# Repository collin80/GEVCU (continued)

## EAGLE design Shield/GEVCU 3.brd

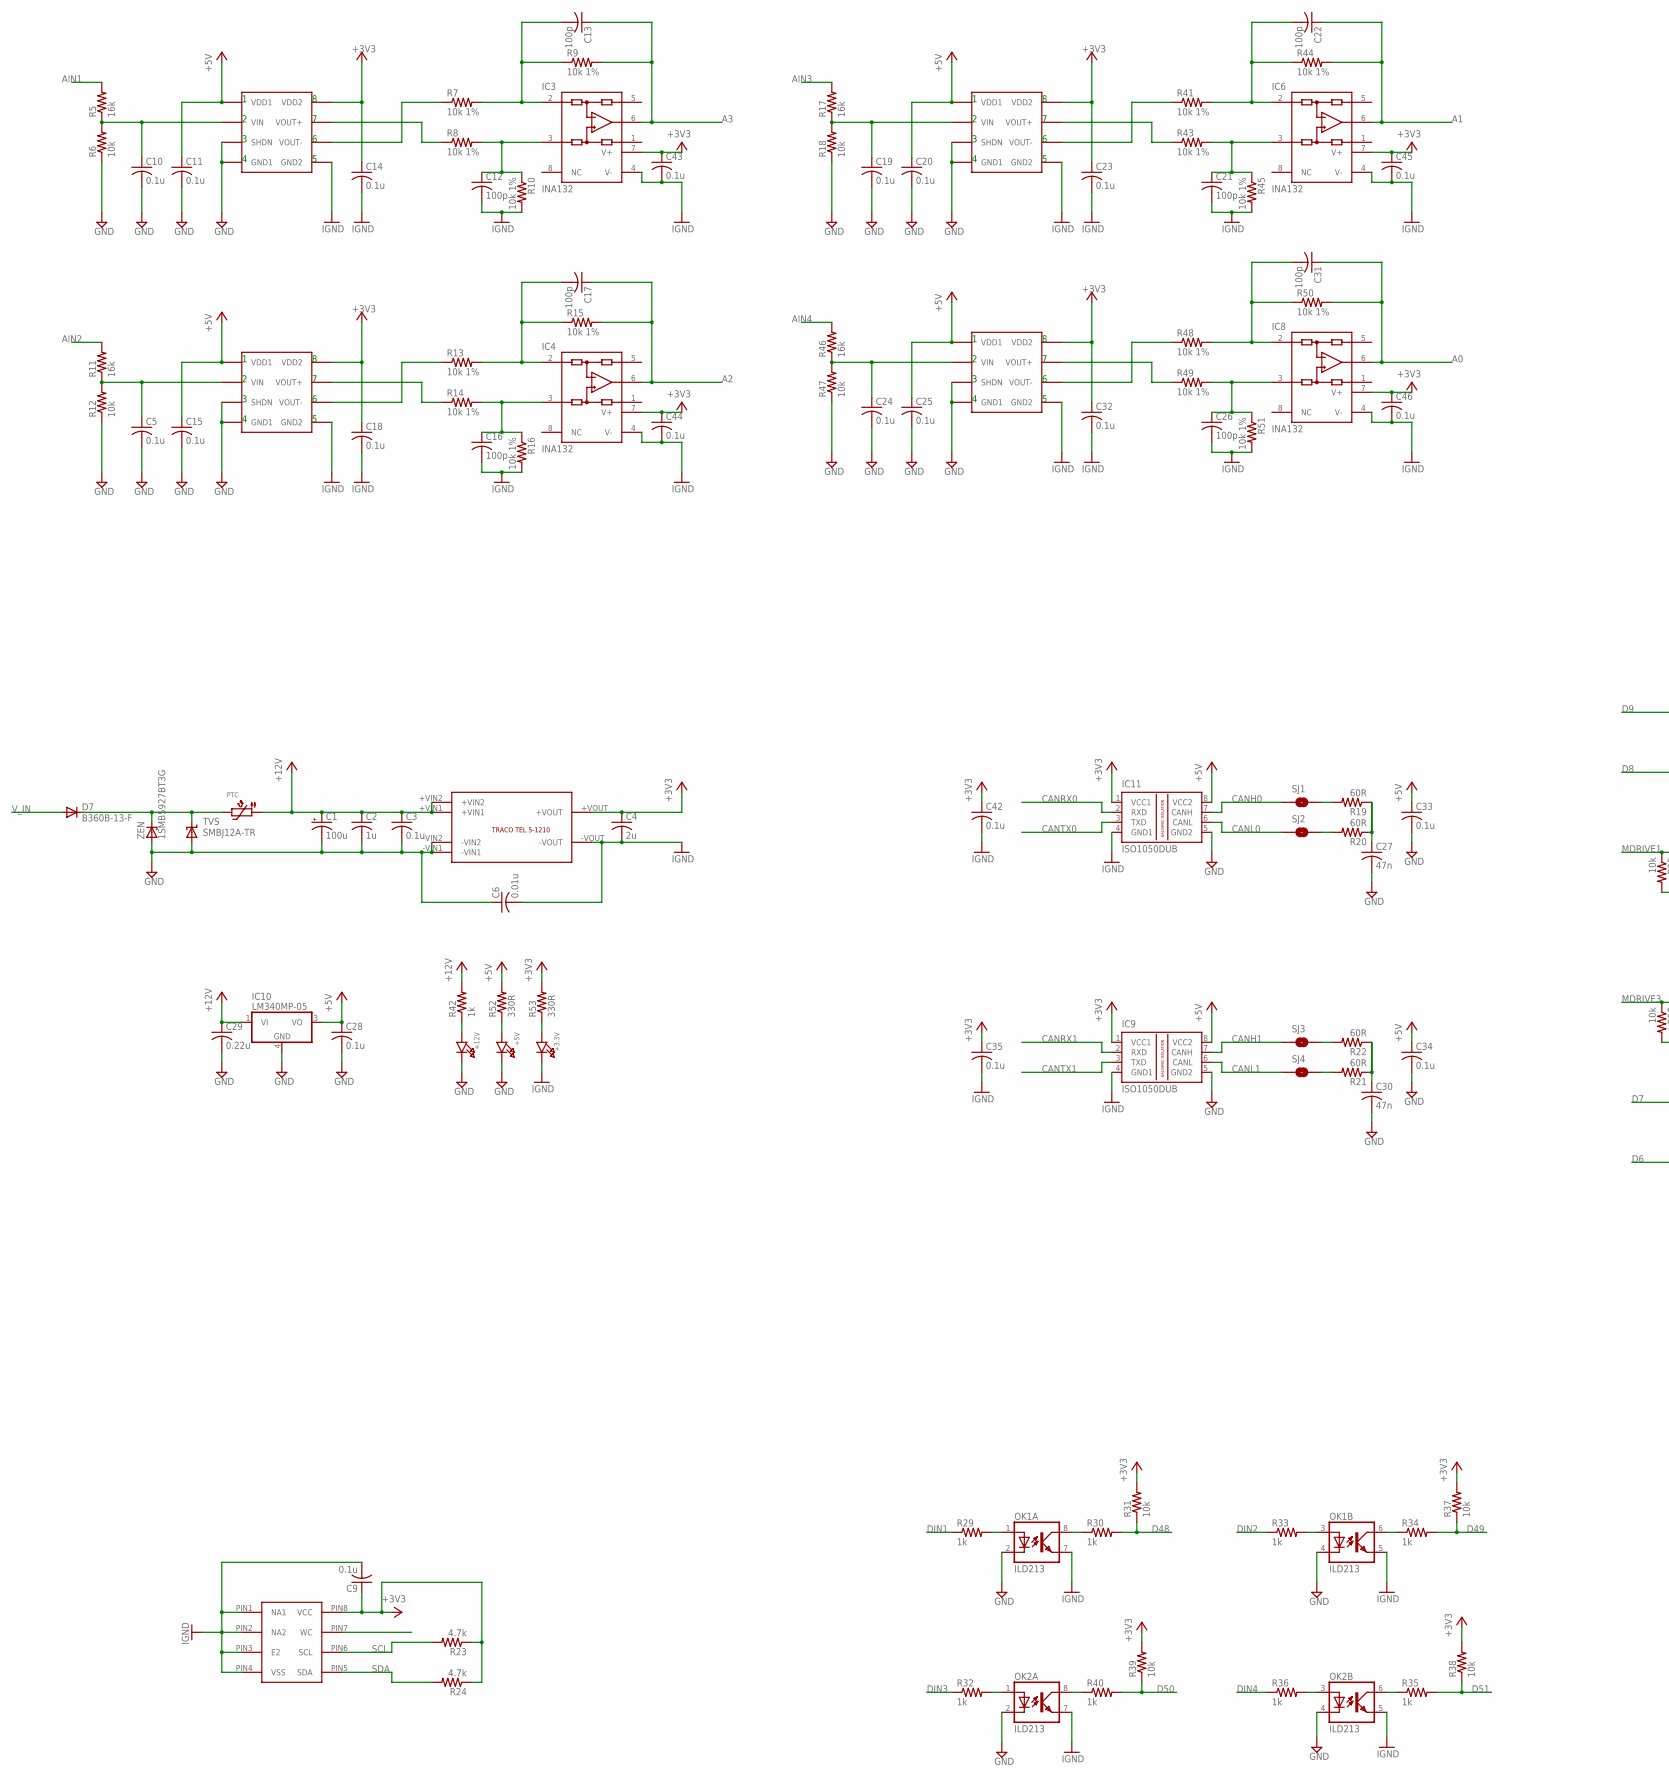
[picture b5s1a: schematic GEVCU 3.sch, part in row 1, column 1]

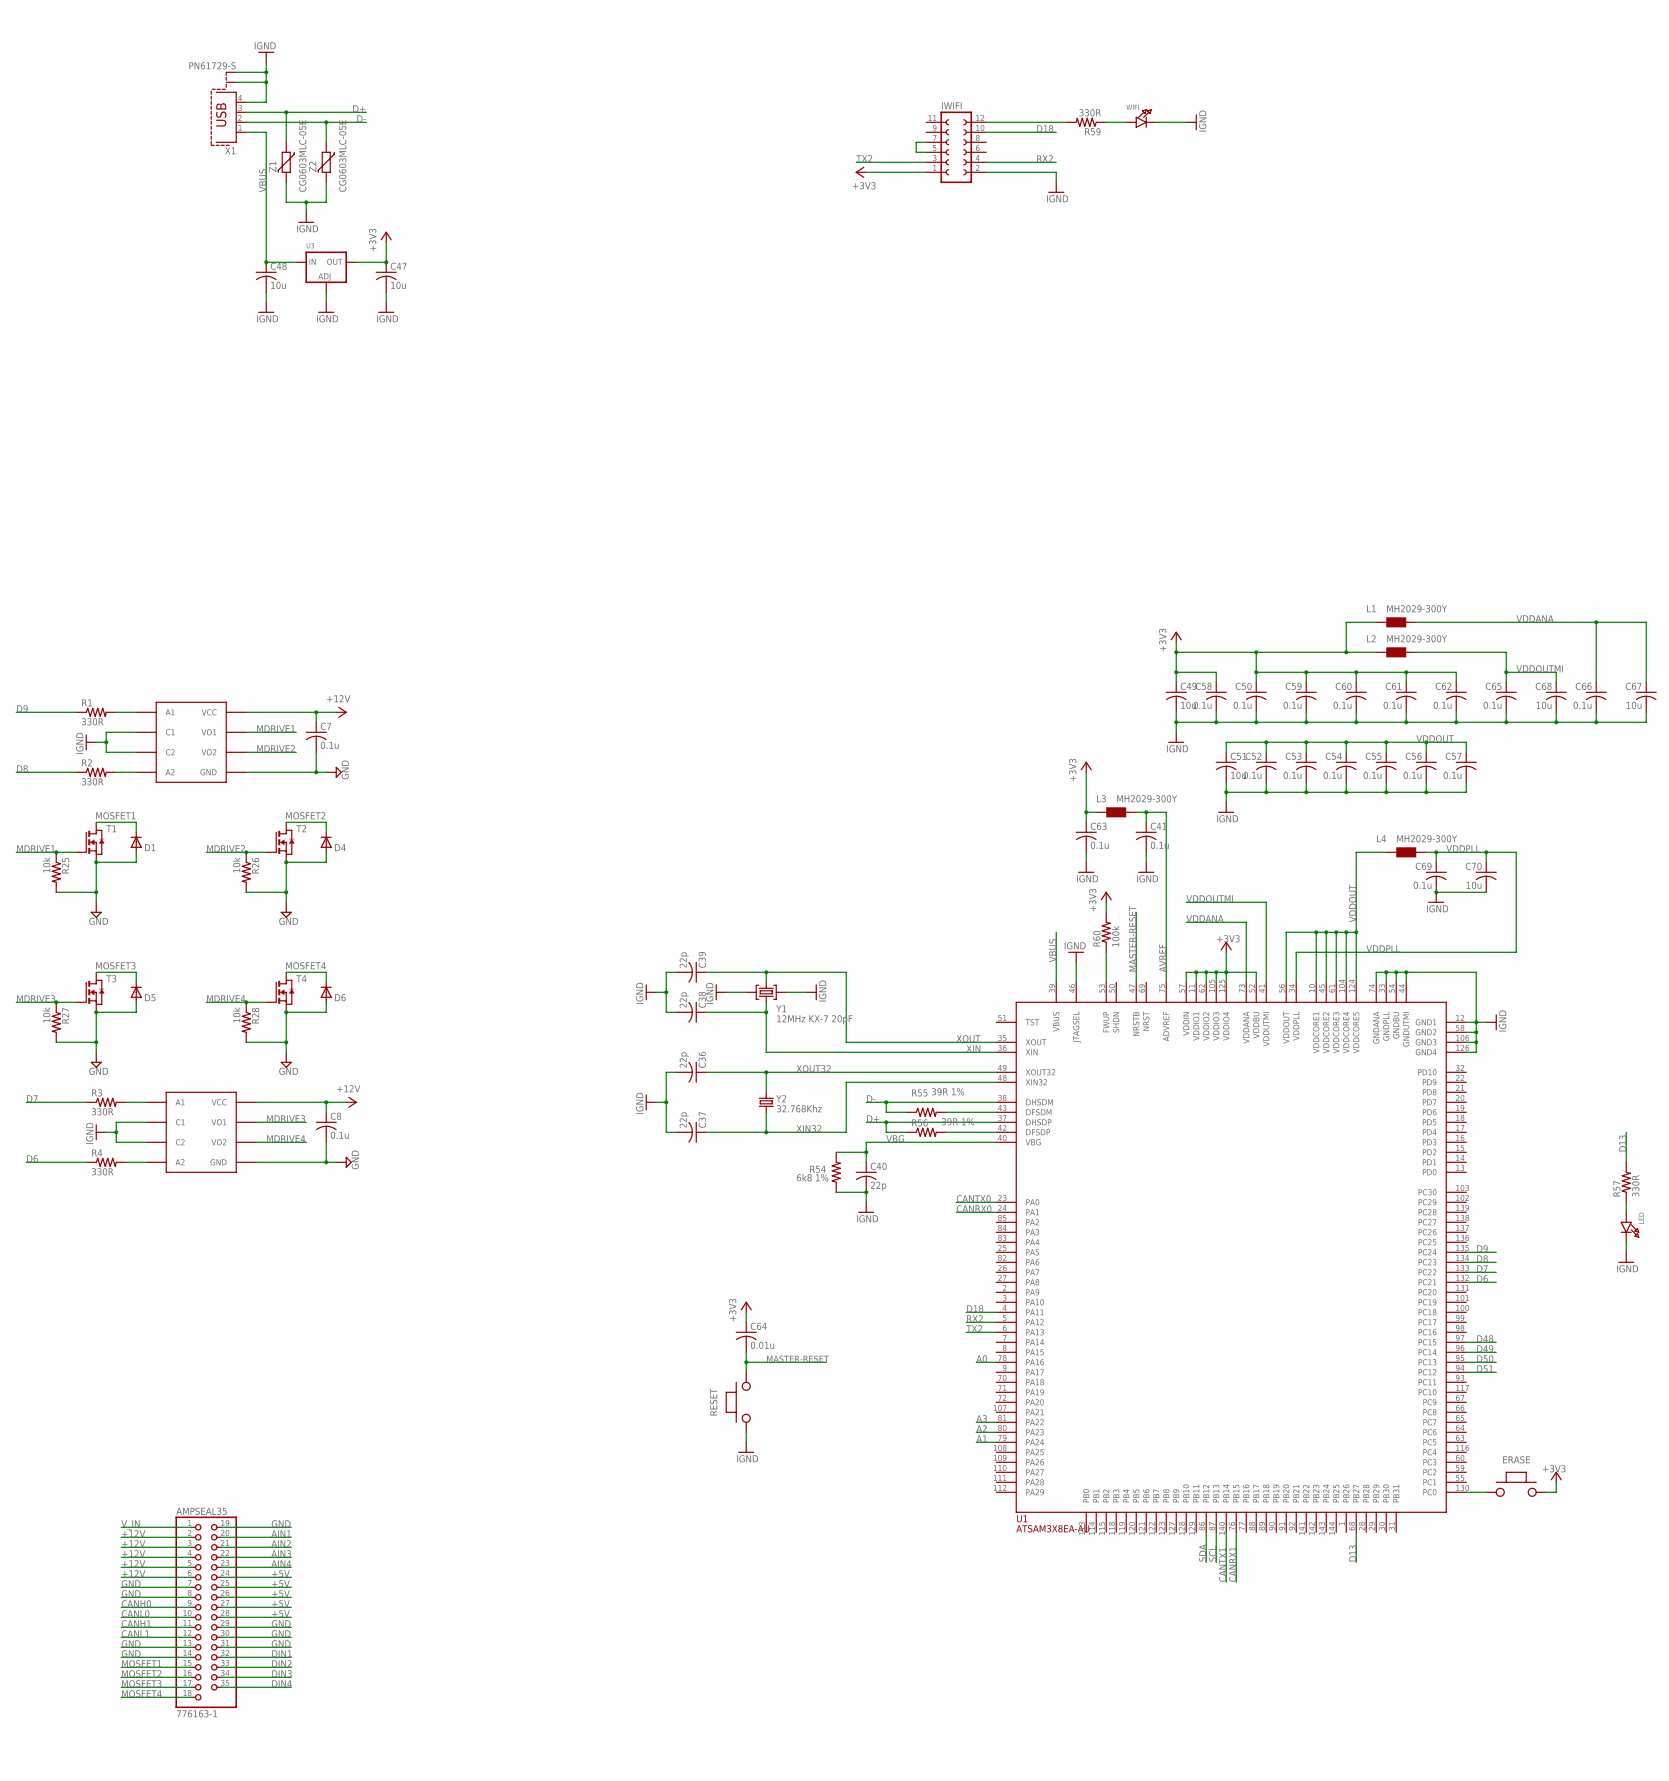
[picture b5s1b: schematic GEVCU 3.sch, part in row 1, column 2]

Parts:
+3.3V, +5V, +12V: LED0805; CHIPLED_0805
AMPSEAL35: 776163-1; AMPSEAL35
C1: 100u; E2,5-6
C2: 1u; C0805
C3, C5, C7, C8, C9, C10, C14, C18, C19, C23, C24, C28, C32, C33, C34, C35, C41, C42, C43, C44, C45, C46, C50, C52, C53, C54, C55, C56, C57, C58, C59, C60, C61, C62, C63, C65, C66, C69: 0.1u; C0805
C4: 2u; C0805
C6: 0.01u; C1812
C11, C15, C20, C25: 0.1u; C1206
C12, C13, C16, C17, C21, C22, C26, C31: 100p; C0805
C27, C30: 47n; C0805
C29: 0.22u; C0805
C36, C37, C40: 22p; C0805
C38, C39: 22p; C1206
C47, C48, C49, C51, C67, C68, C70: 10u; C0805
C64: 0.01u; C0805
D1, D4, D5, D6: MBR0520LT; SOD123
D7: B360B-13-F; SMB
ERASE: PUCHBUTTON
IC1, IC2, IC5, IC7: ACPL-C87A-000E; SO8-WIDE
IC3, IC4, IC6, IC8: INA132; SO08
IC9, IC11: ISO1050DUB; DUB-R-PDSO-G8
IC10: LM340MP-05; SOT223
IWIFI: FE06-2
L1, L2, L3, L4: MH2029-300Y; 0805
LED: LED0805; CHIPLED_0805
OK1, OK2: ILD213; SOIC08
PTC: PTC1812
R1, R2, R3, R4, R52, R53, R57, R59: 330R; R0805
R5, R11, R17, R46: 16k; R0805
R6, R12, R18, R25, R26, R27, R28, R31, R37, R38, R39, R47: 10k; R0805
R7, R8, R9, R10, R13, R14, R15, R16, R41, R43, R44, R45, R48, R49, R50, R51: 10k 1%; R0805
R19, R20, R21, R22: 60R; R0805
R23, R24: 4.7k; R0805
R29, R30, R32, R33, R34, R35, R36, R40, R42: 1k; R0805
R54: 6k8 1%; R0805
R55, R56: 39R 1%; R0805
R60: 100k; R0805
RESET: PUCHBUTTON
SJ1, SJ2, SJ3, SJ4: SOLDERJUMPERNO; SJ_2S-NO
T1, T2, T3, T4: NMOSSOT223; SOT223
TVS: SMBJ12A-TR; SMBJ
U1: ATSAM3X8EA-AU; LQFP144
U3: LM1117SOT223-WAVE; SOT223-W
U4, U5: SFH6731; DIP8
U6: M24M02-DRMN6TP; SOIC8
U$2: TRACO
WIFI: LED0805; CHIPLED_0805
X1: PN61729-S
Y1: 12MHz KX-7 20pF; CRYSTAL-3.2-2.5
Y2: 32.768Khz; RESONATOR_EPSON_FC_145
Z1, Z2: CG0603MLC-05E; CT/CN0603
ZEN: 1SMB5927BT3G; SMB

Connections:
+3V3: C4.1, C9.1, C14.1, C18.1, C23.1, C32.1, C35.1, C42.1, C43.1, C44.1, C45.1, C46.1, C47.1, C49.1, C50.1, C58.1, C59.1, C60.1, C61.1, C62.1, C63.1, C64.1, ERASE.P$2, IC1.8 (VDD2), IC2.8 (VDD2), IC3.7 (V+), IC4.7 (V+), IC5.8 (VDD2), IC6.7 (V+), IC7.8 (VDD2), IC8.7 (V+), IC9.1 (VCC1), IC11.1 (VCC1), IWIFI.1, L1.1, L2.1, L3.1, R23.1, R24.1, R31.2, R37.2, R38.2, R39.2, R53.2, R60.2, U1.11 (VDDIO1), U1.52 (VDDBU), U1.57 (VDDIN), U1.62 (VDDIO2), U1.105 (VDDIO3), U1.125 (VDDIO4), U3.2 (OUT), U6.PIN8 (VCC), U$2.+VOUT
+5V: AMPSEAL35.24, AMPSEAL35.25, AMPSEAL35.26, AMPSEAL35.27, AMPSEAL35.28, C11.1, C15.1, C20.1, C25.1, C28.1, C33.1, C34.1, IC1.1 (VDD1), IC2.1 (VDD1), IC5.1 (VDD1), IC7.1 (VDD1), IC9.8 (VCC2), IC10.3 (VO), IC11.8 (VCC2), R52.2
+12V: AMPSEAL35.2, AMPSEAL35.3, AMPSEAL35.4, AMPSEAL35.5, AMPSEAL35.6, C1.+, C2.1, C3.1, C7.1, C8.1, C29.1, IC10.1 (VI), PTC.P$1 (1), R42.2, U4.8 (VCC), U5.8 (VCC), U$2.+VIN1, U$2.+VIN2
A0: C31.1, IC8.6 (OUT), R50.2, U1.78 (PA16)
A1: C22.1, IC6.6 (OUT), R44.2, U1.79 (PA24)
A2: C17.1, IC4.6 (OUT), R15.2, U1.80 (PA23)
A3: C13.1, IC3.6 (OUT), R9.2, U1.81 (PA22)
AIN1: AMPSEAL35.20, R5.2
AIN2: AMPSEAL35.21, R11.2
AIN3: AMPSEAL35.22, R17.2
AIN4: AMPSEAL35.23, R46.2
AVREF: C41.1, L3.2, U1.75 (ADVREF)
CANH0: AMPSEAL35.9, IC11.7 (CANH), SJ1.1
CANH1: AMPSEAL35.11, IC9.7 (CANH), SJ3.1
CANL0: AMPSEAL35.10, IC11.6 (CANL), SJ2.1
CANL1: AMPSEAL35.12, IC9.6 (CANL), SJ4.1
CANRX0: IC11.2 (RXD), U1.24 (PA1)
CANRX1: IC9.2 (RXD), U1.76 (PB15)
CANTX0: IC11.3 (TXD), U1.23 (PA0)
CANTX1: IC9.3 (TXD), U1.140 (PB14)
D6: R4.1, U1.132 (PC21)
D7: R3.1, U1.133 (PC22)
D8: R2.1, U1.134 (PC23)
D9: R1.1, U1.135 (PC24)
D13: R57.2, U1.68 (PB27)
D18: IWIFI.10, U1.4 (PA11)
D48: R30.2, R31.1, U1.97 (PC15)
D49: R34.2, R37.1, U1.96 (PC14)
D50: R39.1, R40.2, U1.95 (PC13)
D51: R35.2, R38.1, U1.94 (PC12)
D+: R56.1, U1.37 (DHSDP), X1.3, Z1.1
D-: R55.1, U1.38 (DHSDM), X1.2, Z2.1
DIN1: AMPSEAL35.32, R29.1
DIN2: AMPSEAL35.33, R33.1
DIN3: AMPSEAL35.34, R32.1
DIN4: AMPSEAL35.35, R36.1
ERASE_S: ERASE.P$1, U1.130 (PC0)
GND: +5V.C, +12V.C, AMPSEAL35.7, AMPSEAL35.8, AMPSEAL35.13, AMPSEAL35.14, AMPSEAL35.19, AMPSEAL35.29, AMPSEAL35.30, AMPSEAL35.31, C1.-, C2.2, C3.2, C5.2, C6.1, C7.2, C8.2, C10.2, C11.2, C15.2, C19.2, C20.2, C24.2, C25.2, C27.2, C28.2, C29.2, C30.2, C33.2, C34.2, D1.A, D4.A, D5.A, D6.A, IC1.3 (SHDN), IC1.4 (GND1), IC2.3 (SHDN), IC2.4 (GND1), IC5.3 (SHDN), IC5.4 (GND1), IC7.3 (SHDN), IC7.4 (GND1), IC9.5 (GND2), IC10.4 (GND), IC11.5 (GND2), OK1.2 (C), OK1.4 (C), OK2.2 (C), OK2.4 (C), R6.1, R12.1, R18.1, R25.2, R26.2, R27.2, R28.2, R47.1, T1.3 (S), T2.3 (S), T3.3 (S), T4.3 (S), TVS.A, U4.5 (GND), U5.5 (GND), U$2.-VIN1, U$2.-VIN2, ZEN.A
IGND: +3.3V.C, C4.2, C6.2, C9.2, C12.2, C14.2, C16.2, C18.2, C21.2, C23.2, C26.2, C32.2, C35.2, C36.2, C37.2, C38.2, C39.2, C40.2, C41.2, C42.2, C43.2, C44.2, C45.2, C46.2, C47.2, C48.2, C49.2, C50.2, C51.2, C52.2, C53.2, C54.2, C55.2, C56.2, C57.2, C58.2, C59.2, C60.2, C61.2, C62.2, C63.2, C65.2, C66.2, C67.2, C68.2, C69.2, C70.2, IC1.5 (GND2), IC2.5 (GND2), IC3.4 (V-), IC4.4 (V-), IC5.5 (GND2), IC6.4 (V-), IC7.5 (GND2), IC8.4 (V-), IC9.4 (GND1), IC11.4 (GND1), IWIFI.2, LED.C, OK1.5 (EMIT), OK1.7 (EMIT), OK2.5 (EMIT), OK2.7 (EMIT), R10.2, R16.2, R45.2, R51.2, R54.1, RESET.P$1, U1.12 (GND1), U1.33 (GNDPLL), U1.44 (GNDUTMI), U1.46 (JTAGSEL), U1.54 (GNDBU), U1.58 (GND2), U1.74 (GNDANA), U1.106 (GND3), U1.126 (GND4), U3.1 (ADJ), U4.2 (C1), U4.3 (C2), U5.2 (C1), U5.3 (C2), U6.PIN1 (NA1), U6.PIN2 (NA2), U6.PIN3 (E2), U6.PIN4 (VSS), U$2.-VOUT, WIFI.C, X1.4, X1.S1, X1.S2, Y1.2 (GND), Y1.4 (GND), Z1.2, Z2.2
MASTER-RESET: C64.2, RESET.P$2, U1.47 (NRSTB)
MDRIVE1: R25.1, T1.1 (G), U5.7 (VO1)
MDRIVE2: R26.1, T2.1 (G), U5.6 (VO2)
MDRIVE3: R27.1, T3.1 (G), U4.7 (VO1)
MDRIVE4: R28.1, T4.1 (G), U4.6 (VO2)
MOSFET1: AMPSEAL35.15, D1.C, T1.2 (D), T1.4 (D)
MOSFET2: AMPSEAL35.16, D4.C, T2.2 (D), T2.4 (D)
MOSFET3: AMPSEAL35.17, D5.C, T3.2 (D), T3.4 (D)
MOSFET4: AMPSEAL35.18, D6.C, T4.2 (D), T4.4 (D)
unnamed: C10.1, IC1.2 (VIN), R5.1, R6.2
unnamed: +3.3V.A, R53.1
unnamed: D7.C, PTC.P$2 (2), TVS.C, ZEN.C
unnamed: +5V.A, R52.1
unnamed: R3.2, U4.1 (A1)
unnamed: LED.A, R57.1
unnamed: R1.2, U5.1 (A1)
unnamed: IC2.7 (VOUT+), R14.1
unnamed: IC2.6 (VOUT-), R13.1
unnamed: R2.2, U5.4 (A2)
unnamed: R4.2, U4.4 (A2)
unnamed: C17.2, IC4.2 (-IN), R13.2, R15.1
unnamed: IC1.7 (VOUT+), R8.1
unnamed: IC1.6 (VOUT-), R7.1
unnamed: C13.2, IC3.2 (-IN), R7.2, R9.1
unnamed: C12.1, IC3.3 (+IN), R8.2, R10.1
unnamed: C16.1, IC4.3 (+IN), R14.2, R16.1
unnamed: C5.1, IC2.2 (VIN), R11.1, R12.2
unnamed: IC5.7 (VOUT+), R43.1
unnamed: IC5.6 (VOUT-), R41.1
unnamed: C22.2, IC6.2 (-IN), R41.2, R44.1
unnamed: C21.1, IC6.3 (+IN), R43.2, R45.1
unnamed: C19.1, IC5.2 (VIN), R17.1, R18.2
unnamed: C27.1, R19.1, R20.1
unnamed: IC7.7 (VOUT+), R49.1
unnamed: R19.2, SJ1.2
unnamed: R20.2, SJ2.2
unnamed: R21.2, SJ4.2
unnamed: C30.1, R21.1, R22.1
unnamed: R22.2, SJ3.2
unnamed: OK1.1 (A), R29.2
unnamed: OK1.3 (A), R33.2
unnamed: OK1.8 (COL), R30.1
unnamed: OK1.6 (COL), R34.1
unnamed: IC7.6 (VOUT-), R48.1
unnamed: OK2.6 (COL), R35.1
unnamed: C31.2, IC8.2 (-IN), R48.2, R50.1
unnamed: OK2.8 (COL), R40.1
unnamed: C26.1, IC8.3 (+IN), R49.2, R51.1
unnamed: OK2.1 (A), R32.2
unnamed: C24.1, IC7.2 (VIN), R46.1, R47.2
unnamed: OK2.3 (A), R36.2
unnamed: +12V.A, R42.1
unnamed: IWIFI.12, R59.2
unnamed: R59.1, WIFI.A
unnamed: IWIFI.5, IWIFI.7
unnamed: R55.2, U1.43 (DFSDM)
unnamed: R56.2, U1.42 (DFSDP)
unnamed: R60.1, U1.53 (FWUP)
RX2: IWIFI.4, U1.5 (PA12)
RXD1: U6.PIN7 (WC)
SCL: R23.2, U1.87 (PB13), U6.PIN6 (SCL)
SDA: R24.2, U1.86 (PB12), U6.PIN5 (SDA)
TX2: IWIFI.3, U1.6 (PA13)
VBG: C40.1, R54.2, U1.40 (VBG)
VBUS: C48.1, U1.39 (VBUS), U3.3 (IN), X1.1
VDDANA: C66.1, C67.1, L1.2, U1.73 (VDDANA)
VDDOUT: C51.1, C52.1, C53.1, C54.1, C55.1, C56.1, C57.1, L4.1, U1.10 (VDDCORE1), U1.45 (VDDCORE2), U1.56 (VDDOUT), U1.61 (VDDCORE3), U1.104 (VDDCORE4), U1.124 (VDDCORE5)
VDDOUTMI: C65.1, C68.1, L2.2, U1.41 (VDDUTMI)
VDDPLL: C69.1, C70.1, L4.2, U1.34 (VDDPLL)
V_IN: AMPSEAL35.1, D7.A
XIN: C38.1, U1.36 (XIN), Y1.1 (C1)
XIN32: C37.1, U1.48 (XIN32), Y2.P$2 (2)
XOUT: C39.1, U1.35 (XOUT), Y1.3 (C2)
XOUT32: C36.1, U1.49 (XOUT32), Y2.P$1 (1)

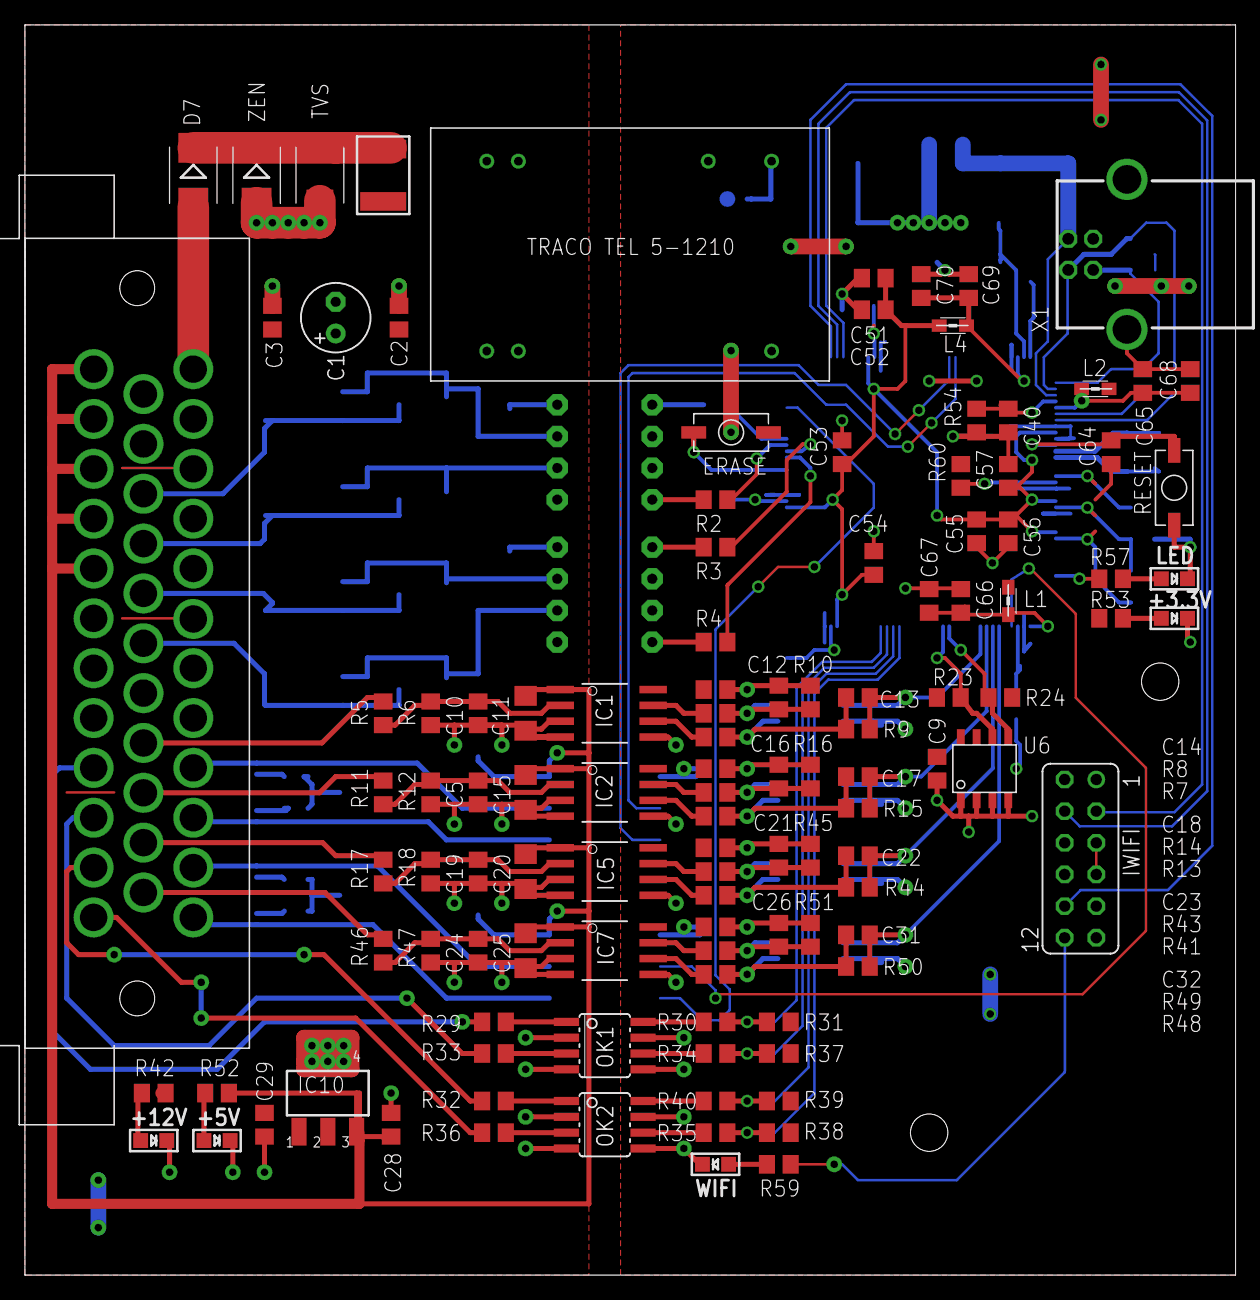
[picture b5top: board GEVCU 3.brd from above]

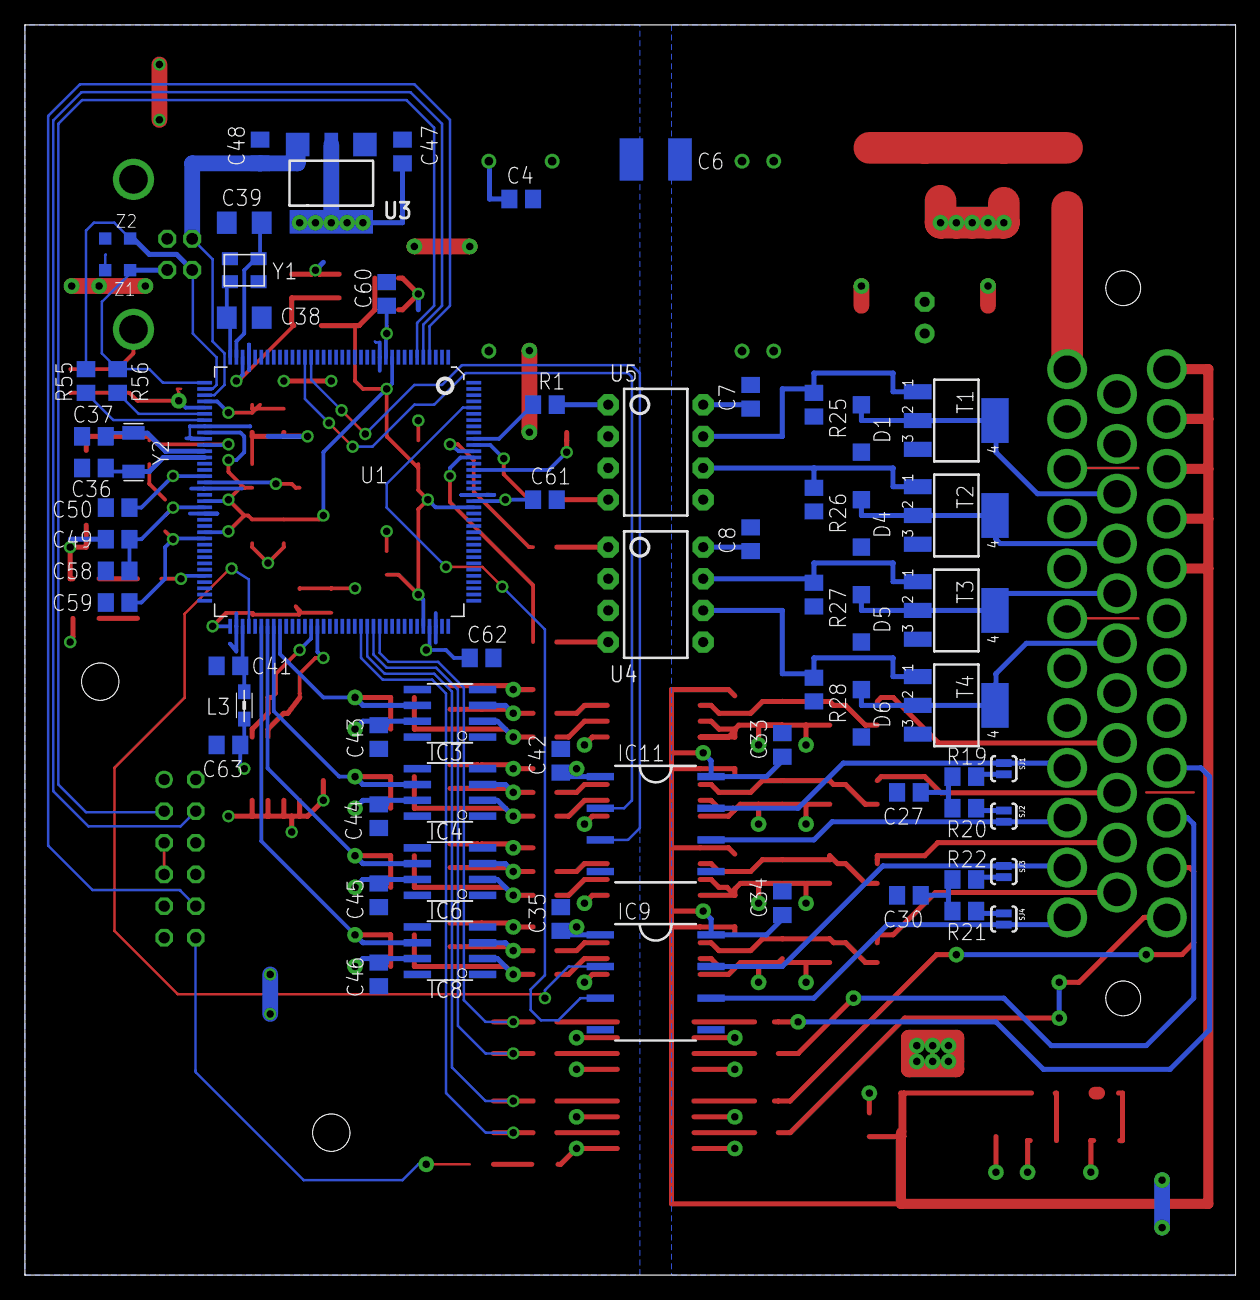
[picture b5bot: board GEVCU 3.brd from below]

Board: 2 copper layers, 97.2 x 100.3 mm, 182 parts (67 on the bottom side), 112 nets.

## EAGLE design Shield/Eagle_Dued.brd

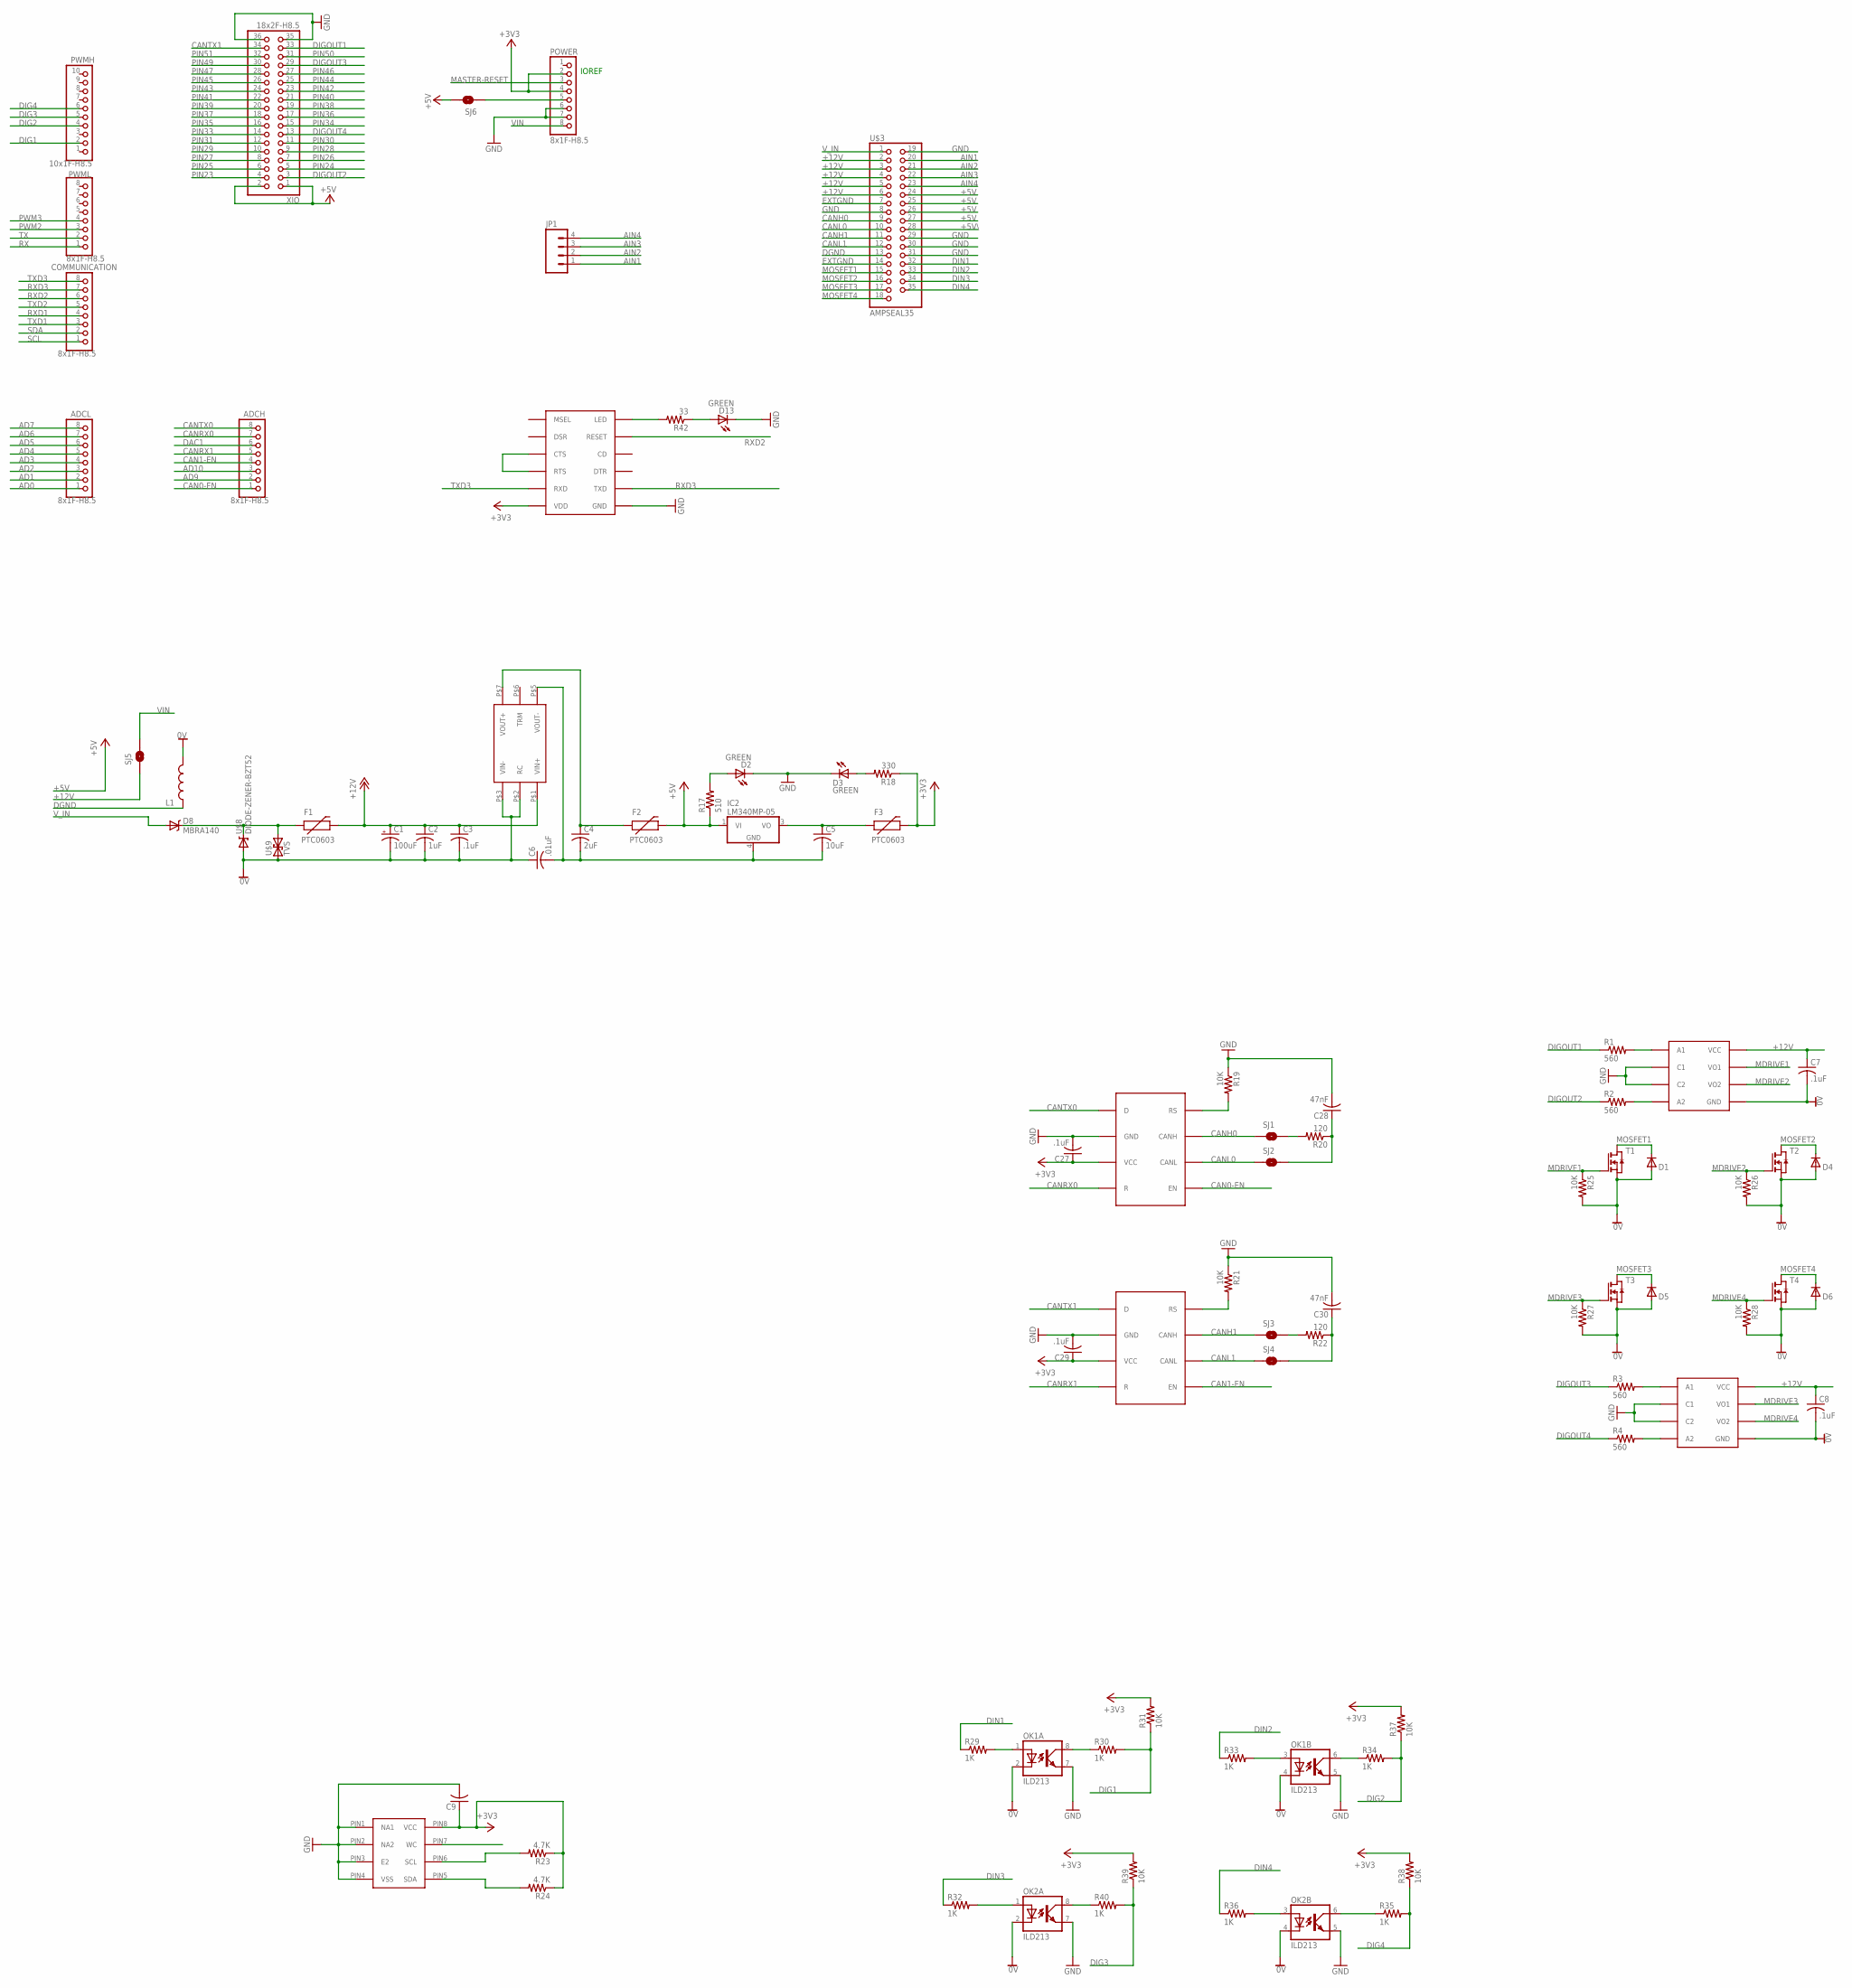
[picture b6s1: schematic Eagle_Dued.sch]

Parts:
ADCH: 8x1F-H8.5; 1X08
ADCL: 8x1F-H8.5; 1X08
C1: 100uF; E2,5-6
C2: 1uF; C1206
C3, C7, C8: .1uF; C1206
C4: 2uF; C0805
C5: 10uF; C1206
C6: .01uF; C1206
C9: C-USC0603; C0603
C27, C29: .1uF; C0603
C28, C30: 47nF; C0603
COMMUNICATION: 8x1F-H8.5; 1X08
D1, D4, D5, D6: MBR0520LT; SOD123
D2, D3, D13: GREEN; LED-0603
D8: MBRA140; SMA-DIODE
F1, F2, F3: PTC0603; 0603
IC2: LM340MP-05; SOT223
JP1: M04POLAR; MOLEX-1X4
L1: INDUCTOR1206H*; INDUCTOR-1206
OK1, OK2: ILD213; SOIC08
POWER: 8x1F-H8.5; 1X08
PWMH: 10x1F-H8.5; 1X10
PWML: 8x1F-H8.5; 1X08
R1, R2, R3, R4: 560; R0603
R17: 510; R0603
R18: 330; R0603
R19, R21, R25, R26, R27, R28, R31, R37, R38, R39: 10K; R0603
R20, R22: 120; R0603
R23, R24: 4.7K; R0603
R29, R30, R32, R33, R34, R35, R36, R40: 1K; R0603
R42: 33; R0603
SJ1, SJ2, SJ3, SJ4, SJ5, SJ6: SOLDERJUMPERNO; SJ_2S-NO
T1, T2, T3, T4: NMOSSOT223; SOT223
U$1: CC3-E
U$2, U$6: SN65HVD234; SOIC8
U$3: AMPSEAL35
U$4: MINIWIFI
U$5: M24M02-DRMN6TP; SOIC8
U$7, U$10: SFH6731; DIP8
U$8: DIODE-ZENER-BZT52; SOD-323
U$9: TVS; SMA-DIODE
XIO: 18x2F-H8.5; 2X18

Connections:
0V: C7.2, C8.2, OK1.2 (C), OK1.4 (C), OK2.2 (C), OK2.4 (C), U$7.5 (GND), U$10.5 (GND)
+3V3: C9.1, C27.1, C29.1, F3.2, POWER.2, POWER.4, R18.1, R23.1, R24.1, R31.2, R37.2, R38.2, R39.2, U$2.PIN3 (VCC), U$4.P$1 (VDD), U$5.PIN8 (VCC), U$6.PIN3 (VCC)
+5V: F2.2, IC2.1 (VI), R17.1, SJ6.2, U$3.24, U$3.25, U$3.26, U$3.27, XIO.1, XIO.2
+5V\: U$3.28
+12V: C1.+, C2.1, C3.1, C7.1, C8.1, F1.2, SJ5.1, U$1.P$1 (VIN+), U$3.2, U$3.3, U$3.4, U$3.5, U$3.6, U$7.8 (VCC), U$10.8 (VCC)
AD0: ADCL.1
AD1: ADCL.2
AD2: ADCL.3
AD3: ADCL.4
AD4: ADCL.5
AD5: ADCL.6
AD6: ADCL.7
AD7: ADCL.8
AD9: ADCH.2
AD10: ADCH.3
AIN1: JP1.1, U$3.20
AIN2: JP1.2, U$3.21
AIN3: JP1.3, U$3.22
AIN4: JP1.4, U$3.23
CAN0-EN: ADCH.1, U$6.PIN5 (EN)
CAN1-EN: ADCH.4, U$2.PIN5 (EN)
CANH0: SJ1.1, U$3.9, U$6.PIN7 (CANH)
CANH1: SJ3.1, U$2.PIN7 (CANH), U$3.11
CANL0: SJ2.1, U$3.10, U$6.PIN6 (CANL)
CANL1: SJ4.1, U$2.PIN6 (CANL), U$3.12
CANRX0: ADCH.7, U$6.PIN4 (R)
CANRX1: ADCH.5, U$2.PIN4 (R)
CANTX0: ADCH.8, U$6.PIN1 (D)
CANTX1: U$2.PIN1 (D), XIO.34
DAC1: ADCH.6
DGND: L1.P$1 (1), U$3.13
DIG1: PWMH.2, R30.2, R31.1
DIG2: PWMH.4, R34.2, R37.1
DIG3: PWMH.5, R39.1, R40.2
DIG4: PWMH.6, R35.2, R38.1
DIGOUT1: R1.1, XIO.33
DIGOUT2: R2.1, XIO.3
DIGOUT3: R3.1, XIO.29
DIGOUT4: R4.1, XIO.13
DIN1: R29.1, U$3.32
DIN2: R33.1, U$3.33
DIN3: R32.1, U$3.34
DIN4: R36.1, U$3.35
EXTGND: C1.-, C2.2, C3.2, C6.1, D1.A, D4.A, D5.A, D6.A, L1.P$2 (2), R25.2, R26.2, R27.2, R28.2, T1.3 (S), T2.3 (S), T3.3 (S), T4.3 (S), U$1.P$2 (RC), U$1.P$3 (VIN-), U$3.7, U$3.14, U$8.2 (A), U$9.A (1)
GND: C4.2, C5.2, C6.2, C9.2, C27.2, C28.2, C29.2, C30.2, D2.C, D3.C, D13.C, IC2.4 (GND), OK1.5 (EMIT), OK1.7 (EMIT), OK2.5 (EMIT), OK2.7 (EMIT), POWER.6, POWER.7, R19.1, R21.1, U$1.P$5 (VOUT-), U$2.PIN2 (GND), U$3.8, U$3.19, U$3.29, U$3.30, U$3.31, U$4.P$2 (GND), U$5.PIN1 (NA1), U$5.PIN2 (NA2), U$5.PIN3 (E2), U$5.PIN4 (VSS), U$6.PIN2 (GND), U$7.2 (C1), U$7.3 (C2), U$10.2 (C1), U$10.3 (C2), XIO.35, XIO.36
MASTER-RESET: POWER.3
MDRIVE1: R25.1, T1.1 (G), U$10.7 (VO1)
MDRIVE2: R26.1, T2.1 (G), U$10.6 (VO2)
MDRIVE3: R27.1, T3.1 (G), U$7.7 (VO1)
MDRIVE4: R28.1, T4.1 (G), U$7.6 (VO2)
MOSFET1: D1.C, T1.2 (D), T1.4 (D), U$3.15
MOSFET2: D4.C, T2.2 (D), T2.4 (D), U$3.16
MOSFET3: D5.C, T3.2 (D), T3.4 (D), U$3.17
MOSFET4: D6.C, T4.2 (D), T4.4 (D), U$3.18
unnamed: POWER.5, SJ6.1
unnamed: U$4.P$5 (RTS), U$4.P$7 (CTS)
unnamed: D8.C, F1.1, U$8.1 (C), U$9.C (2)
unnamed: R42.2, U$4.P$12 (LED)
unnamed: R3.2, U$7.1 (A1)
unnamed: C4.1, F2.1, U$1.P$7 (VOUT+)
unnamed: R1.2, U$10.1 (A1)
unnamed: C5.1, F3.1, IC2.3 (VO)
unnamed: D13.A, R42.1
unnamed: R2.2, U$10.4 (A2)
unnamed: R4.2, U$7.4 (A2)
unnamed: D2.A, R17.2
unnamed: R19.2, U$6.PIN8 (RS)
unnamed: D3.A, R18.2
unnamed: C28.1, R20.1, SJ2.2
unnamed: R20.2, SJ1.2
unnamed: R21.2, U$2.PIN8 (RS)
unnamed: C30.1, R22.1, SJ4.2
unnamed: R22.2, SJ3.2
unnamed: OK1.1 (A), R29.2
unnamed: OK1.3 (A), R33.2
unnamed: OK1.8 (COL), R30.1
unnamed: OK1.6 (COL), R34.1
unnamed: OK2.6 (COL), R35.1
unnamed: OK2.8 (COL), R40.1
unnamed: OK2.1 (A), R32.2
unnamed: OK2.3 (A), R36.2
PIN23: XIO.4
PIN24: XIO.5
PIN25: XIO.6
PIN26: XIO.7
PIN27: XIO.8
PIN28: XIO.9
PIN29: XIO.10
PIN30: XIO.11
PIN31: XIO.12
PIN33: XIO.14
PIN34: XIO.15
PIN35: XIO.16
PIN36: XIO.17
PIN37: XIO.18
PIN38: XIO.19
PIN39: XIO.20
PIN40: XIO.21
PIN41: XIO.22
PIN42: XIO.23
PIN43: XIO.24
PIN44: XIO.25
PIN45: XIO.26
PIN46: XIO.27
PIN47: XIO.28
PIN49: XIO.30
PIN50: XIO.31
PIN51: XIO.32
PWM2: PWML.3
PWM3: PWML.4
RX: PWML.1
RXD1: COMMUNICATION.4, U$5.PIN7 (WC)
RXD2: COMMUNICATION.6, U$4.P$10 (RESET)
RXD3: COMMUNICATION.7, U$4.P$4 (TXD)
SCL: COMMUNICATION.1, R23.2, U$5.PIN6 (SCL)
SDA: COMMUNICATION.2, R24.2, U$5.PIN5 (SDA)
TX: PWML.2
TXD1: COMMUNICATION.3
TXD2: COMMUNICATION.5
TXD3: COMMUNICATION.8, U$4.P$3 (RXD)
VIN: POWER.8, SJ5.2
V_IN: D8.A, U$3.1

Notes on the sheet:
IOREF
